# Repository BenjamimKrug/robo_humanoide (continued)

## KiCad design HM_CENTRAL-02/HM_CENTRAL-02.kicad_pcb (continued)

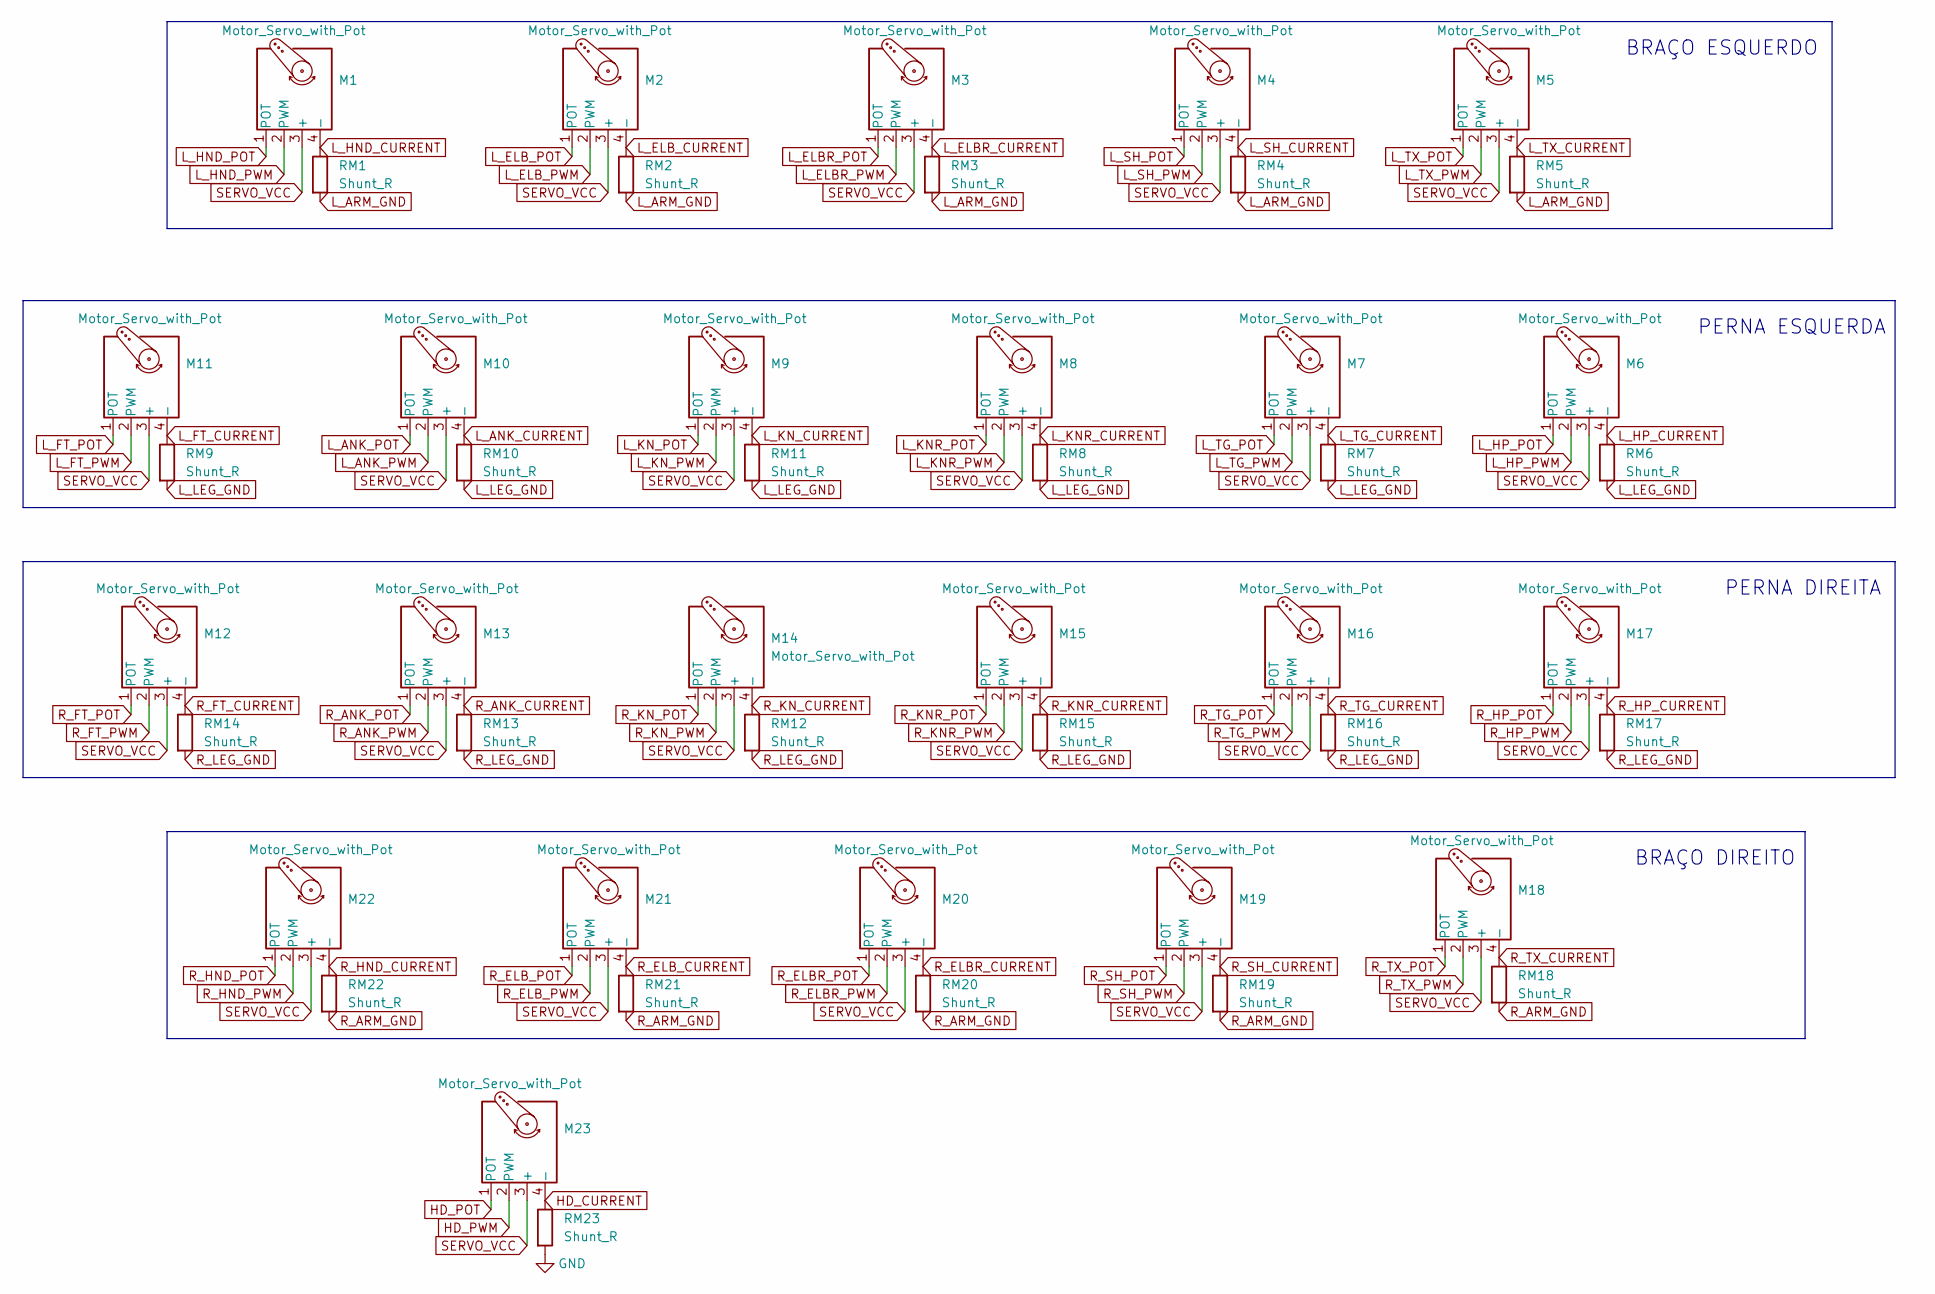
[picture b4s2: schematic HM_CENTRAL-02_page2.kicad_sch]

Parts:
M1, M2, M3, M4, M5, M6, M7, M8, M9, M10, M11, M12, M13, M14, M15, M16, M17, M18, M19, M20, M21, M22, M23: Motor_Servo_with_Pot; PinHeader_1x04_P2.54mm_Vertical
RM1, RM2, RM3, RM4, RM5, RM6, RM7, RM8, RM9, RM10, RM11, RM12, RM13, RM14, RM15, RM16, RM17, RM18, RM19, RM20, RM21, RM22: Shunt_R; R_Axial_DIN0204_L3.6mm_D1.6mm_P2.54mm_Vertical
RM23: Shunt_R; R_Axial_DIN0204_L3.6mm_D1.6mm_P5.08mm_Horizontal

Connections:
GND: RM23.2; also elsewhere on the board
HD_CURRENT: M23.4 (-), RM23.1; also elsewhere on the board
HD_POT: M23.1 (POT); also elsewhere on the board
HD_PWM: M23.2 (PWM); also elsewhere on the board
L_ANK_CURRENT: M10.4 (-), RM10.1; also elsewhere on the board
L_ANK_POT: M10.1 (POT); also elsewhere on the board
L_ANK_PWM: M10.2 (PWM); also elsewhere on the board
L_ARM_GND: RM1.2, RM2.2, RM3.2, RM4.2, RM5.2; also elsewhere on the board
L_ELBR_CURRENT: M3.4 (-), RM3.1; also elsewhere on the board
L_ELBR_POT: M3.1 (POT); also elsewhere on the board
L_ELBR_PWM: M3.2 (PWM); also elsewhere on the board
L_ELB_CURRENT: M2.4 (-), RM2.1; also elsewhere on the board
L_ELB_POT: M2.1 (POT); also elsewhere on the board
L_ELB_PWM: M2.2 (PWM); also elsewhere on the board
L_FT_CURRENT: M11.4 (-), RM9.1; also elsewhere on the board
L_FT_POT: M11.1 (POT); also elsewhere on the board
L_FT_PWM: M11.2 (PWM); also elsewhere on the board
L_HND_CURRENT: M1.4 (-), RM1.1; also elsewhere on the board
L_HND_POT: M1.1 (POT); also elsewhere on the board
L_HND_PWM: M1.2 (PWM); also elsewhere on the board
L_HP_CURRENT: M6.4 (-), RM6.1; also elsewhere on the board
L_HP_POT: M6.1 (POT); also elsewhere on the board
L_HP_PWM: M6.2 (PWM); also elsewhere on the board
L_KNR_CURRENT: M8.4 (-), RM8.1; also elsewhere on the board
L_KNR_POT: M8.1 (POT); also elsewhere on the board
L_KNR_PWM: M8.2 (PWM); also elsewhere on the board
L_KN_CURRENT: M9.4 (-), RM11.1; also elsewhere on the board
L_KN_POT: M9.1 (POT); also elsewhere on the board
L_KN_PWM: M9.2 (PWM); also elsewhere on the board
L_LEG_GND: RM6.2, RM7.2, RM8.2, RM9.2, RM10.2, RM11.2; also elsewhere on the board
L_SH_CURRENT: M4.4 (-), RM4.1; also elsewhere on the board
L_SH_POT: M4.1 (POT); also elsewhere on the board
L_SH_PWM: M4.2 (PWM); also elsewhere on the board
L_TG_CURRENT: M7.4 (-), RM7.1; also elsewhere on the board
L_TG_POT: M7.1 (POT); also elsewhere on the board
L_TG_PWM: M7.2 (PWM); also elsewhere on the board
L_TX_CURRENT: M5.4 (-), RM5.1; also elsewhere on the board
L_TX_POT: M5.1 (POT); also elsewhere on the board
L_TX_PWM: M5.2 (PWM); also elsewhere on the board
R_ANK_CURRENT: M13.4 (-), RM13.1; also elsewhere on the board
R_ANK_POT: M13.1 (POT); also elsewhere on the board
R_ANK_PWM: M13.2 (PWM); also elsewhere on the board
R_ARM_GND: RM18.2, RM19.2, RM20.2, RM21.2, RM22.2; also elsewhere on the board
R_ELBR_CURRENT: M20.4 (-), RM20.1; also elsewhere on the board
R_ELBR_POT: M20.1 (POT); also elsewhere on the board
R_ELBR_PWM: M20.2 (PWM); also elsewhere on the board
R_ELB_CURRENT: M21.4 (-), RM21.1; also elsewhere on the board
R_ELB_POT: M21.1 (POT); also elsewhere on the board
R_ELB_PWM: M21.2 (PWM); also elsewhere on the board
R_FT_CURRENT: M12.4 (-), RM14.1; also elsewhere on the board
R_FT_POT: M12.1 (POT); also elsewhere on the board
R_FT_PWM: M12.2 (PWM); also elsewhere on the board
R_HND_CURRENT: M22.4 (-), RM22.1; also elsewhere on the board
R_HND_POT: M22.1 (POT); also elsewhere on the board
R_HND_PWM: M22.2 (PWM); also elsewhere on the board
R_HP_CURRENT: M17.4 (-), RM17.1; also elsewhere on the board
R_HP_POT: M17.1 (POT); also elsewhere on the board
R_HP_PWM: M17.2 (PWM); also elsewhere on the board
R_KNR_CURRENT: M15.4 (-), RM15.1; also elsewhere on the board
R_KNR_POT: M15.1 (POT); also elsewhere on the board
R_KNR_PWM: M15.2 (PWM); also elsewhere on the board
R_KN_CURRENT: M14.4 (-), RM12.1; also elsewhere on the board
R_KN_POT: M14.1 (POT); also elsewhere on the board
R_KN_PWM: M14.2 (PWM); also elsewhere on the board
R_LEG_GND: RM12.2, RM13.2, RM14.2, RM15.2, RM16.2, RM17.2; also elsewhere on the board
R_SH_CURRENT: M19.4 (-), RM19.1; also elsewhere on the board
R_SH_POT: M19.1 (POT); also elsewhere on the board
R_SH_PWM: M19.2 (PWM); also elsewhere on the board
R_TG_CURRENT: M16.4 (-), RM16.1; also elsewhere on the board
R_TG_POT: M16.1 (POT); also elsewhere on the board
R_TG_PWM: M16.2 (PWM); also elsewhere on the board
R_TX_CURRENT: M18.4 (-), RM18.1; also elsewhere on the board
R_TX_POT: M18.1 (POT); also elsewhere on the board
R_TX_PWM: M18.2 (PWM); also elsewhere on the board
SERVO_VCC: M1.3 (+), M2.3 (+), M3.3 (+), M4.3 (+), M5.3 (+), M6.3 (+), M7.3 (+), M8.3 (+), M9.3 (+), M10.3 (+), M11.3 (+), M12.3 (+), M13.3 (+), M14.3 (+), M15.3 (+), M16.3 (+), M17.3 (+), M18.3 (+), M19.3 (+), M20.3 (+), M21.3 (+), M22.3 (+), M23.3 (+); also elsewhere on the board

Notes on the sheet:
BRAÇO ESQUERDO
PERNA ESQUERDA
PERNA DIREITA
BRAÇO DIREITO

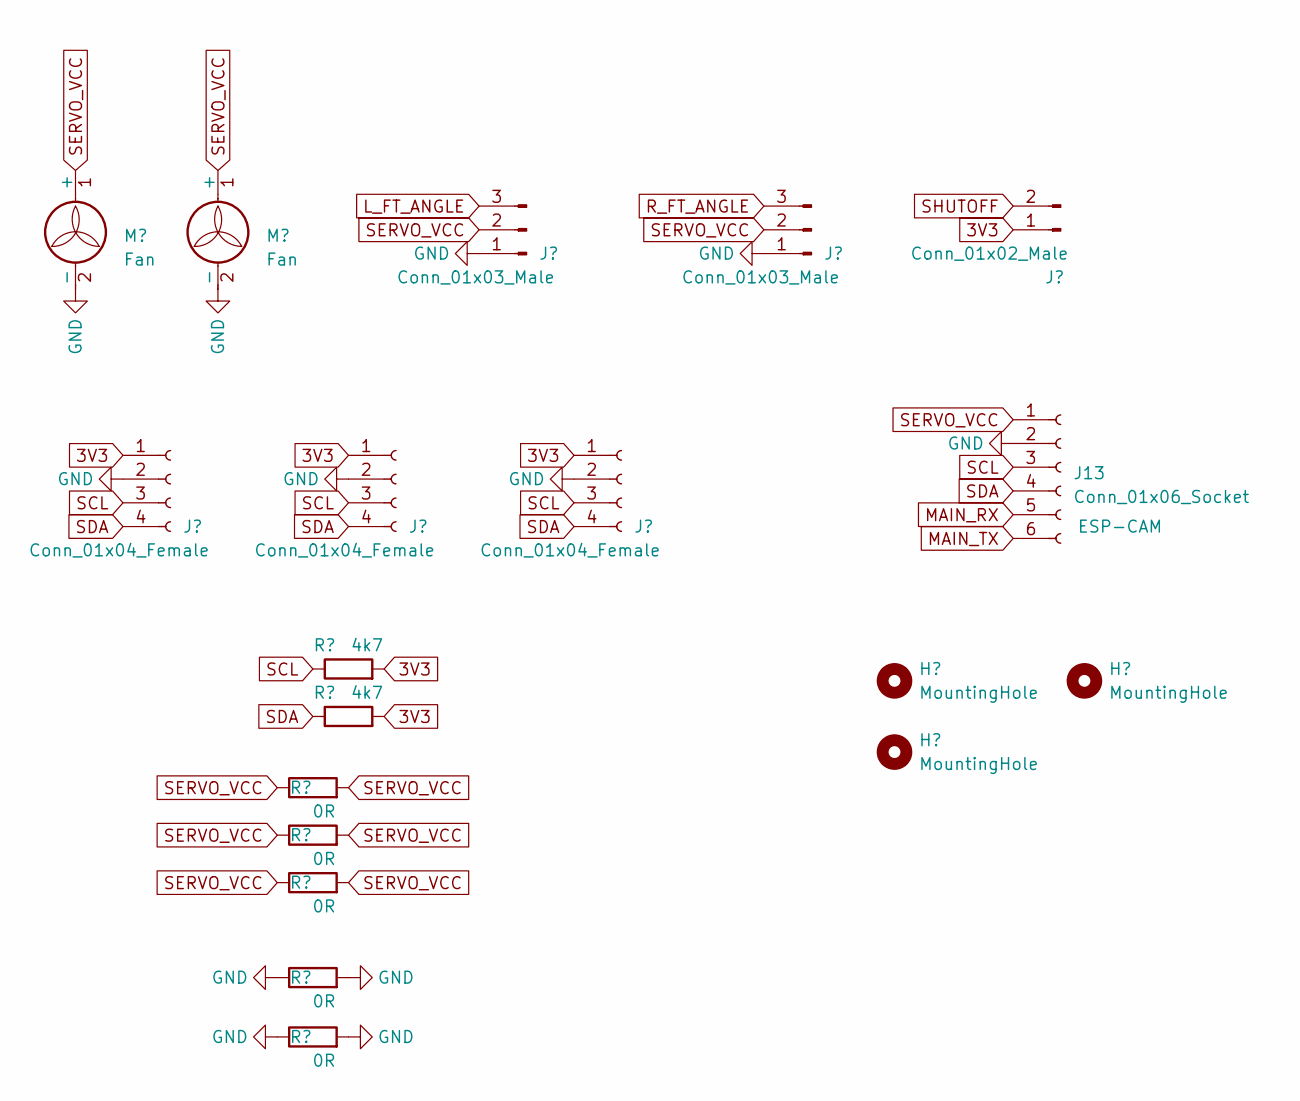
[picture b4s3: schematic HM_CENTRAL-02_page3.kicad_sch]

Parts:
H1, H2, H3: MountingHole; MountingHole_3.2mm_M3
J5, J6: Conn_01x03_Male; PinHeader_1x03_P2.54mm_Vertical
J7: Conn_01x02_Male; TestPoint_2Pads_Pitch5.08mm_Drill1.3mm
J8, J9, J10: Conn_01x04_Female; PinSocket_1x04_P2.54mm_Vertical
J13: Conn_01x06_Socket; PinSocket_1x06_P2.54mm_Vertical
M24, M25: Fan; PinHeader_1x02_P2.54mm_Vertical
R11, R12, R13, R16, R17: 0R; R_Axial_DIN0207_L6.3mm_D2.5mm_P7.62mm_Horizontal
R38, R39: 4k7; R_Axial_DIN0207_L6.3mm_D2.5mm_P7.62mm_Horizontal

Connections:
3V3: J7.1, J8.1, J9.1, J10.1, R38.2, R39.2; also elsewhere on the board
GND: J5.1, J6.1, J8.2, J9.2, J10.2, J13.2, M24.2 (-), M25.2 (-), R13.1, R13.2, R16.1, R16.2; also elsewhere on the board
L_FT_ANGLE: J5.3; also elsewhere on the board
MAIN_RX: J13.5; also elsewhere on the board
MAIN_TX: J13.6; also elsewhere on the board
R_FT_ANGLE: J6.3; also elsewhere on the board
SCL: J8.3, J9.3, J10.3, J13.3, R38.1; also elsewhere on the board
SDA: J8.4, J9.4, J10.4, J13.4, R39.1; also elsewhere on the board
SERVO_VCC: J5.2, J6.2, J13.1, M24.1 (+), M25.1 (+), R11.1, R11.2, R12.1, R12.2, R17.1, R17.2; also elsewhere on the board
SHUTOFF: J7.2; also elsewhere on the board

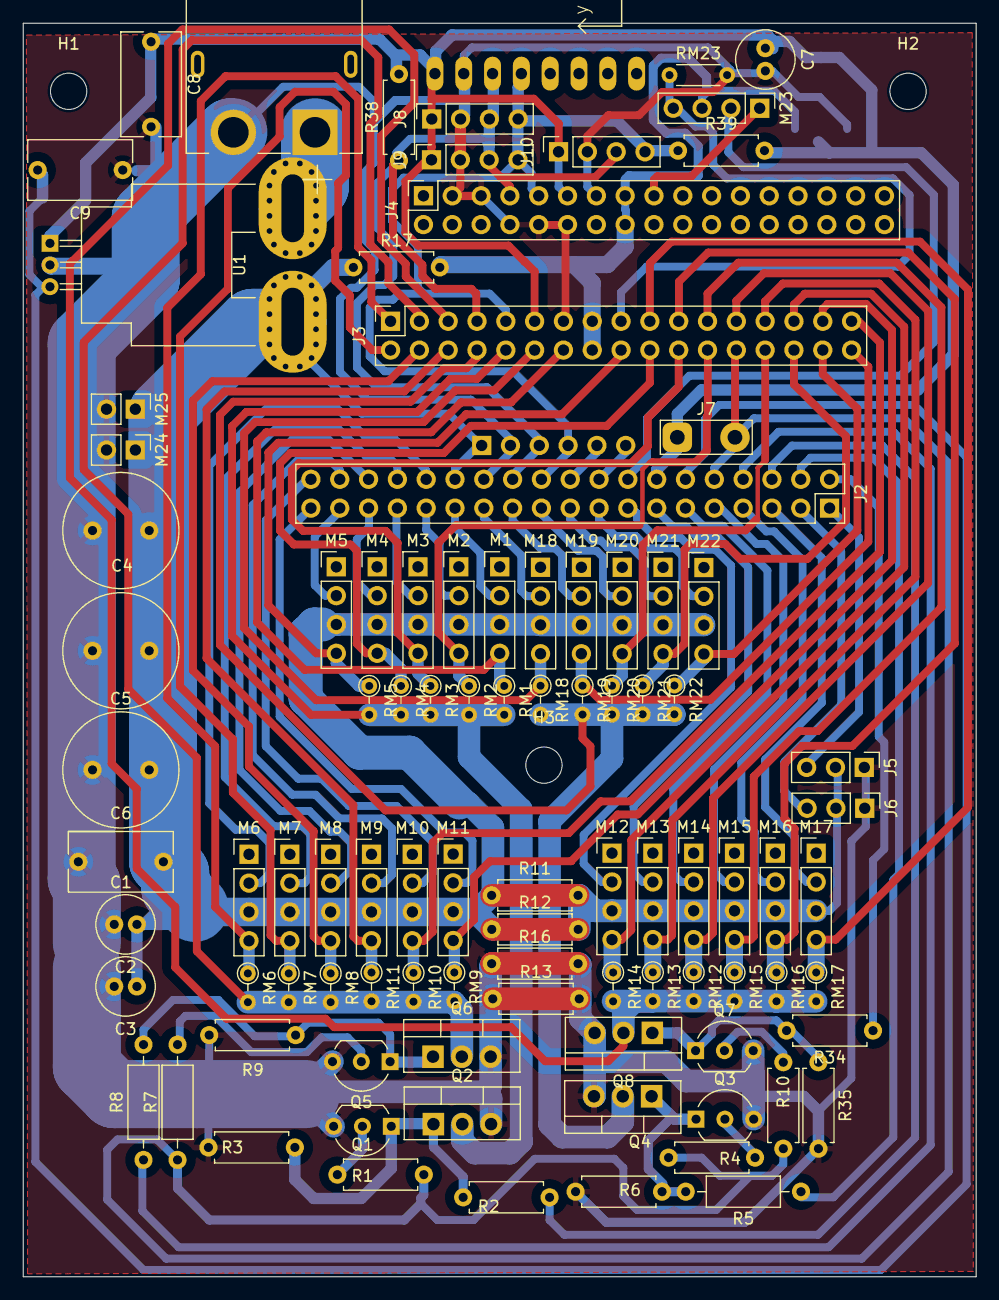
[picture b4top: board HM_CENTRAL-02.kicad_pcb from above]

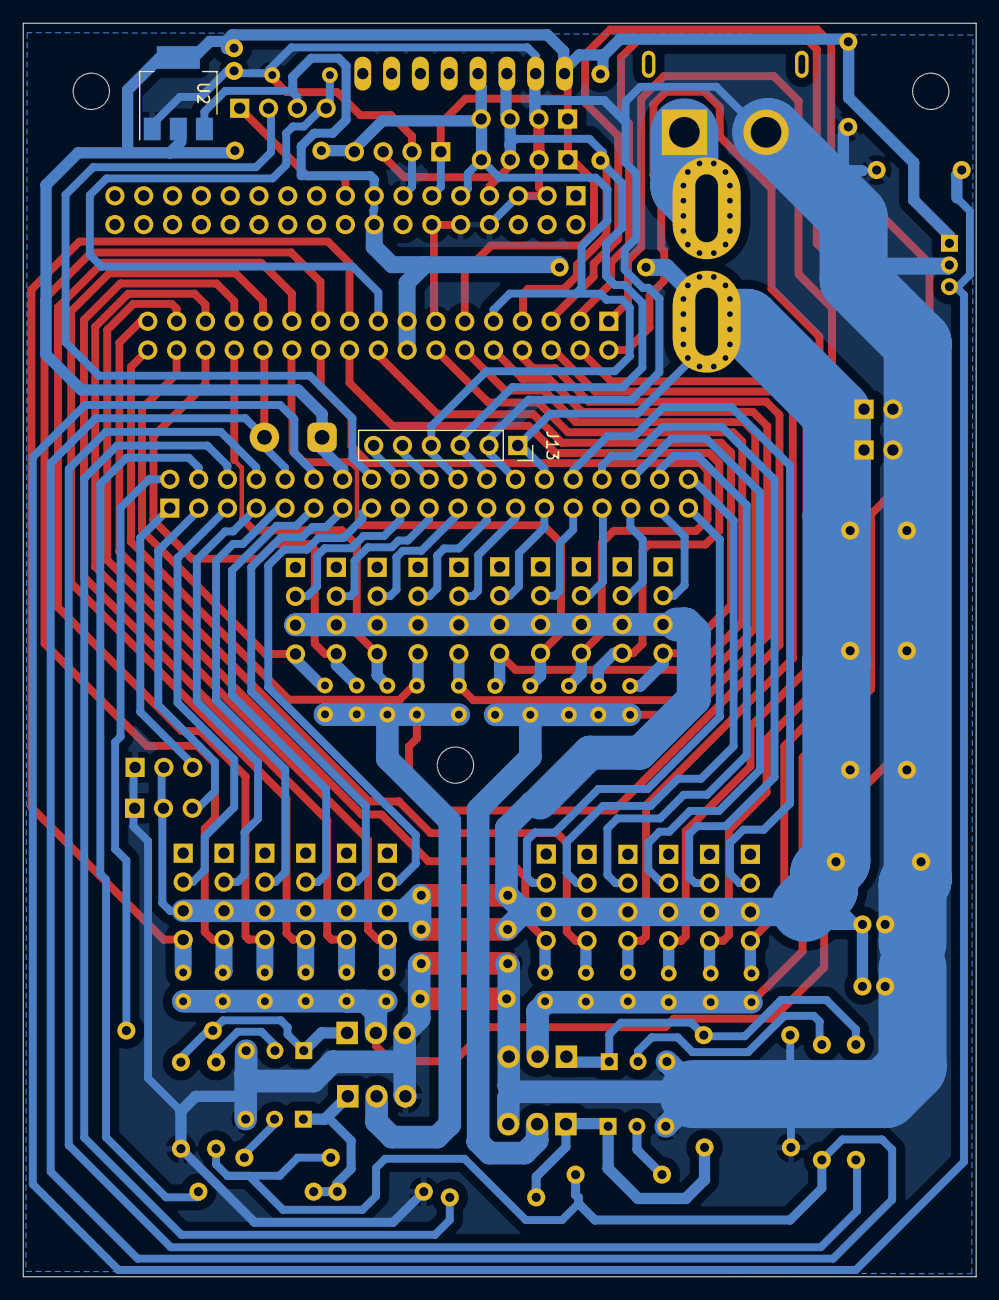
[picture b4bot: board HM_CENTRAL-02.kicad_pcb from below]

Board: 4 copper layers, 84.0 x 110.5 mm, 101 parts (2 on the bottom side), 97 nets.

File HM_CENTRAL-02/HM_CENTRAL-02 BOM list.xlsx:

Referência | Quantidade | Modelo / Valor
C1, C8, C9 | 3.0 | capacitor de poliester de 100nF 6V ou mais
C2 | 1.0 | capacitor eletrolítico de 10uF 6V ou mais
C3, C7 | 2.0 | capacitor eletrolítico de 100uF 6V ou mais
C4, C5 | 2.0 | capacitor eletrolítico de 1800uF 6V ou mais
C6 | 1.0 | capacitor eletrolítico de 2200uF 6V ou mais
J1 | 1.0 | XT60 fêmea para cabo ou com pinos em 90°
J2 | 1.0 | Barra de pinos fêmea simples de 2 x 19 ou 2 barras de 1 x 19
J3, J4 | 2.0 | Barra de pinos fêmea simples de 2 x 17 ou 2 barras de 1 x 17
J5, J6 | 2.0 | Barra de pinos macho(12mm de comprimento) de 1 x 3
J7 | 1.0 | Barra de pinos macho(12mm de comprimento) de 1 x 3
J8, J9, J10 | 3.0 | Barra de pinos fêmea simples de 1 x 4
J13 | 1.0 | Barra de pinos fêmea simples de 1 x 6
M1 - M23 | 23.0 | Barra de pinos macho(12mm de comprimento) de 1 x 4
M24, M25 | 2.0 | Barra de pinos macho(12mm de comprimento) de 1 x 2
Q1, Q3, Q5, Q7 | 4.0 | BC337 TO-92
Q2, Q4, Q6, Q8 | 4.0 | IRFZ44N TO-220
R1, R4, R7, R10 | 4.0 | resistor de 1K 1/4W
R2, R5, R8, R34 | 4.0 | resistor de 33K 1/4W
R3, R6, R9, R35 | 4.0 | resistor de 330K 1/4W
R11, R12, R13, R16, R17 | 5.0 | resistor de 0R ou 1 pino de uma Barra de pinos de 20mm de comprimento
R38, R39 | 2.0 | resistor de 4k7 1/4W
RM1 - RM23 | 23.0 | Shunt_R = resistor de 0,1 ohm 1W
U1 | 1.0 | ACS758xCB-050B-PFF
U2 | 1.0 | AMS1117-3.3
U3 | 1.0 | GY-521 / MPU6050

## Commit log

2023-05-14 commit inicial dos códigos
2023-07-14 adicionando pcb central
2023-08-10 demarcados os pads que precisam dos rebites ocos
2023-08-22 adicionados padrões de furos para os furos grandes
2023-08-25 adicionado código de teste do mpu6050
2023-09-08 placa do processador principal com ESP32 projetada
2023-09-08 adicionado painel
2023-09-09 placa do processador principal com ESP32 WROOM (SMD) adicionada
2023-09-20 adicionadas imagens dos pads com rebites
2023-09-25 arrumado código de teste do MPU e modelo dos diodos adicionado
2023-09-26 firmware de teste pwm da placa do processador central
2023-09-30 codigo atualizado para teste da placa main
2024-04-19 adicionados gerbers da pcb do ESP dev
2024-04-29 adicionadas peças de medição de angulo dos servo motores
2024-04-30 medidores ajustados para melhor impressão e estrutura adicionada
2024-05-01 3d da placa do esp dev adicionada e chifre do sg90
2024-05-01 adicionada referencia e peças dos pés
2024-05-01 chifre centralizado na junta e junta reduzida levemente
2024-05-03 peças da junta alteradas para melhorar giro e encaixe uma com a outra
2024-06-27 estrutura para o sg90 adicionada
2024-06-28 peças da junta de SG90 exportadas para teste
2024-06-29 arrumando junta com o SG90 baseado na primeira impressão
2024-06-29 código de medição da linearidade do MG995
2024-06-30 range ajustado no medidor de angulo do MG995
2024-06-30 adicionado código de medição dos angulos do SG90 e ajustes para segunda versão da junta do SG90
2024-07-02 inicio do código de controle preciso do servo motor
2024-07-02 junta adicionada na frente do pé
2024-07-03 começo do código de conversão da tabela de compensação
2024-07-04 [UPD] script de criação do arquivo dos arrays de compensação
2024-07-04 [UPD] lógica de controle do servo motor funcional e [FIX] geração dos últimos valores da tabela de angulo
2024-07-07 encaixe das peças atualizado
2024-07-09 adicionada peça de afastamento para a coxa
2024-07-12 junta de conexão da coxa adicionada
2024-07-13 junta da coxa no sentido correto
2024-07-14 adicionado demo de controles diferentes dos servos
2024-07-17 adicionada contagem de ciclos para execução de cada método de calculo do duty cycle
2024-07-19 adicionado controle linear na demo e moldes para papel e poliestireno dos medidores de angulo
2024-07-19 detalhes arrumados para renderizar os medidores de angulo
2024-08-24 adicionada BOM para a placa HM_MAIN_ESP32_DEV-01
2024-12-24 [ADD] leia-me básico para o projeto
2025-01-05 criadas instâncias dos servo motores para replicar as pernas no projeto em 3d
2025-01-06 iniciadao torax do robô
2025-01-07 versão inicial dos braços basicamente projetada
2025-01-08 estrutura do peitoral do robô projetada
2025-01-11 centralizados os furos de baixo da base do sg90
2025-01-14 adicionado encaixe da chave na base do servo e arrumado furo da conexão do ombro
2025-01-26 ajustada peça do peitoral para encaixar a conexão do shutoff
2025-03-04 arrumando normais das peças da estrutura
2025-03-04 corrigindo opção ativada para mostrar normais no .blend
